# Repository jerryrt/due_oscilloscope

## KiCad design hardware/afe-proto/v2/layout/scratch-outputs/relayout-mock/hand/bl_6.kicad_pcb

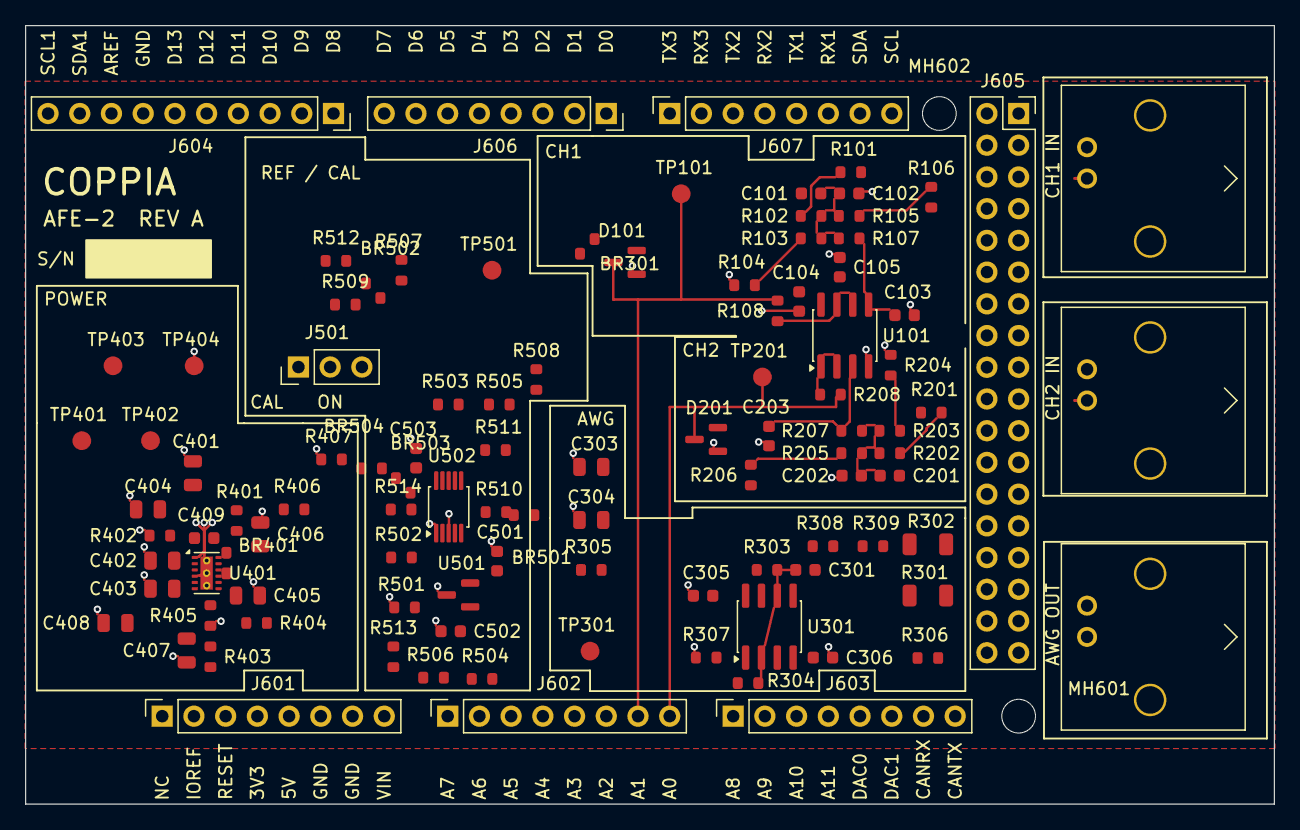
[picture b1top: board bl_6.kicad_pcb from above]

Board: 2 copper layers, 100.0 x 62.3 mm, 105 parts (0 on the bottom side), 54 nets.

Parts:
BR301, BR401, BR501, BR502, BR503, BR504: 0R; R_0603_1608Metric
C101, C201: 18p C0G; C_0603_1608Metric
C102, C202: 47p C0G; C_0603_1608Metric
C103, C203, C301: 10p C0G; C_0603_1608Metric
C104, C305, C306, C502, C503: 100n X7R; C_0603_1608Metric
C105, C409, C501: 1u X5R; C_0603_1608Metric
C303, C304, C401, C402, C403, C404, C405, C406, C407, C408: 10u X5R 25V; C_0805_2012Metric
D101, D201: BAV99; SOT-23
J101, J201, J301: KH-BNC50-3511; BNC_Kinghelm_KH-BNC50-3511_Horizontal
J501: CAL; PinHeader_1x03_P2.54mm_Vertical
J601: POWER0; PinSocket_1x08_P2.54mm_Vertical
J602: ADCL0; PinSocket_1x08_P2.54mm_Vertical
J603: ADCH0; PinSocket_1x08_P2.54mm_Vertical
J604: PWMH0; PinSocket_1x10_P2.54mm_Vertical
J605: XIO0; PinSocket_2x18_P2.54mm_Vertical_DueXIO
J606: PWML0; PinSocket_1x08_P2.54mm_Vertical
J607: COMMUNICATION0; PinSocket_1x08_P2.54mm_Vertical
MH601, MH602: M2.5 standoff; MountingHole_2.7mm_M2.5
R101, R103, R201, R203: 470k 1%; R_0603_1608Metric
R102, R202: 300k 1%; R_0603_1608Metric
R104, R105, R204, R205: 330k 1%; R_0603_1608Metric
R106, R206, R514: 0R; R_0603_1608Metric
R107, R207: 470R 1%; R_0603_1608Metric
R108, R208: 22R 1%; R_0603_1608Metric
R301, R302: 100R 1%; R_1206_3216Metric
R303, R304, R306: 3k 1%; R_0603_1608Metric
R305: 150R 1%; R_0603_1608Metric
R307: 27k 1%; R_0603_1608Metric
R308, R309, R406: 1R 1%; R_0603_1608Metric
R401: 120k 1%; R_0603_1608Metric
R402: 68k 1%; R_0603_1608Metric
R403: 56k 1%; R_0603_1608Metric
R404: 8.2k 1%; R_0603_1608Metric
R405: 100k 1%; R_0603_1608Metric
R407: 1.8k 1%; R_0603_1608Metric
R501, R502, R503, R504, R505, R506: 330R 1%; R_0603_1608Metric
R507: 15k 1%; R_0603_1608Metric
R508, R511: 10k 1%; R_0603_1608Metric
R509: 1k 1%; R_0603_1608Metric
R510: 3.9k 1%; R_0603_1608Metric
R512, R513: 4.7k 1%; R_0603_1608Metric
TP101: A1; TestPoint_Pad_D1.5mm
TP201: A0; TestPoint_Pad_D1.5mm
TP301: AWG_OUT; TestPoint_Pad_D1.5mm
TP401: +3V3A; TestPoint_Pad_D1.5mm
TP402: VNEG; TestPoint_Pad_D1.5mm
TP403: +5V_F; TestPoint_Pad_D1.5mm
TP404: GND; TestPoint_Pad_D1.5mm
TP501: VREF; TestPoint_Pad_D1.5mm
U101, U301: TPH2502-SR; SOIC-8_3.9x4.9mm_P1.27mm
U401: LM27762DSSR; WSON-12-1EP_3x2mm_P0.5mm_EP1x2.65_ThermalVias
U501: REF3030EAIDBZR; SOT-23
U502: ADS1115IDGSR; MSOP-10_3x3mm_P0.5mm

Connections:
/+3V3A: C104.1, C105.1, C305.1, C405.1, C406.1, C502.1, C503.1, D101.2, D201.2, R401.1, R407.1, R512.1, R513.1, TP401.1, U101.8, U301.8, U401.11, U501.1, U502.8
/+5V_DUE: J601.5, R406.1
/+5V_F: C401.1, C402.1, R406.2, TP403.1, U401.3, U401.8, U401.12
/A0: D201.3, J602.8, R208.2, TP201.1
/A1: D101.3, J602.7, R108.2, TP101.1
/ADS_B: R511.2, U502.7
/ADS_TAP: R510.2, U502.6
/AREF: BR504.1, J604.8
/AREF_BR503: BR503.2, R514.2
/AREF_BR504: BR503.1, BR504.2
/AWG_BIN: R306.2, R307.1, U301.3, U301.5
/AWG_BNC: BR301.1, J301.1, R301.2, R302.2
/AWG_BNC_BR301: BR301.2, R507.1
/AWG_FB: C301.2, R303.2, R304.1, U301.2, U301.6
/AWG_OA: R308.1, U301.1
/AWG_OB: R309.1, U301.7
/AWG_VO: C301.1, R301.1, R302.1, R303.1, R308.2, R309.2, TP301.1
/AWG_VREF: C303.1, C304.1, R304.2, R305.2
/CH1_IN: C101.1, J101.1, R101.1
/CH1_M1: R101.2, R102.1
/CH1_M2: R103.2, R104.1
/CH1_M3: R105.2, R106.1
/CH1_N: C101.2, C102.1, R102.2, R103.1, R105.1, R107.1
/CH1_NP: C103.1, R107.2, U101.5
/CH1_OUT: R108.1, U101.6, U101.7
/CH2_IN: C201.1, J201.1, R201.1
/CH2_M1: R201.2, R202.1
/CH2_M2: R203.2, R204.1
/CH2_M3: R205.2, R206.1
/CH2_N: C201.2, C202.1, R202.2, R203.1, R205.1, R207.1
/CH2_NP: C203.1, R207.2, U101.3
/CH2_OUT: R208.1, U101.1, U101.2
/DAC0: J603.5, R306.1
/GND: C102.2, C103.2, C104.2, C105.2, C202.2, C203.2, C303.2, C304.2, C305.2, C306.2, C401.2, C402.2, C403.2, C404.2, C405.2, C406.2, C407.2, C408.2, C501.2, C502.2, C503.2, D101.1, D201.1, J101.2, J201.2, J301.2, J601.6, J601.7, J604.7, J605.35, J605.36, R104.2, R204.2, R307.2, R402.2, R405.2, R407.2, R501.1, TP404.1, U101.4, U401.1, U401.4, U401.13, U501.3, U502.1, U502.3
/LM_C1N: C409.2, U401.9
/LM_C1P: BR401.1, C409.1
/LM_C1P_BR401: BR401.2, U401.10
/LM_CP: C403.1, C404.1, U401.5
/LM_FB3M: R403.2, R404.1
/LM_FBN: R404.2, R405.1, U401.7
/LM_FBP: R401.2, R402.1, U401.2
/SCL: J604.10, R513.2, U502.10
/SDA: BR502.1, J604.9, R512.2
/SDA_BR502: BR502.2, U502.9
/SNS_B: J501.2, R508.2, R509.1, R511.1
/SNS_T0: R507.2, R508.1, R510.1
/TAP1: J602.6, R501.2, R502.1
/TAP2: J602.5, R502.2, R503.1
/TAP3: J501.3, J602.4, R503.2, R504.1
/TAP4: J501.1, J602.3, R504.2, R505.1, U502.5
/TAP5: BR501.1, J602.2, R506.1
/TAP5_BR501: BR501.2, R505.2
/VNEG: C306.1, C407.1, C408.1, R403.1, TP402.1, U301.4, U401.6
/VREF: C501.1, J602.1, R106.2, R206.2, R305.1, R506.2, R509.2, R514.1, TP501.1, U501.2, U502.4

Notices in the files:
hardware/afe-proto/v2/layout/scratch-outputs/relayout-mock/hand/bl_6.kicad_pcb:
Own work, CC BY-SA 4.0
